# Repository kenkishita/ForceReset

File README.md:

#Arduino Force Reset  
This board has been connected between SWP1 of the RPi_SoftSwitch and Reset Pin of the Arduino (need soldering).  
The Foldarap-chimera is full controlled by OctoPrint, ATX power distribute control included. So, the Marlin firmware set up power off the initial,  and send M80 by Octoprint when connected.  
And, I added small program which send the M81 (Turn off Power Supply) after stopping of the Octoprint. But, sometime, it didn't work because connection failure of the /dev/ttyACM0.  
  
This board send reset signal to the arduino simultaneously without any side effect.   

##License Information

These files are free; you can redistribute them and/or modify them under the
terms of the Creative Commons Attribution-ShareAlike 4.0 International
License only, as published by the Creative Commons organization.  

These files are distributed in the hope that they will be useful, but
WITHOUT ANY WARRANTY; without even the implied warranty of MERCHANTABILITY
or FITNESS FOR A PARTICULAR PURPOSE.  See the Creative Commons Attribution-
ShareAlike 4.0 International License for more details.  

Please contact Aynik technology Co., Ltd. at kkishita@aynik-tech.jp if you need additional information or have any questions.

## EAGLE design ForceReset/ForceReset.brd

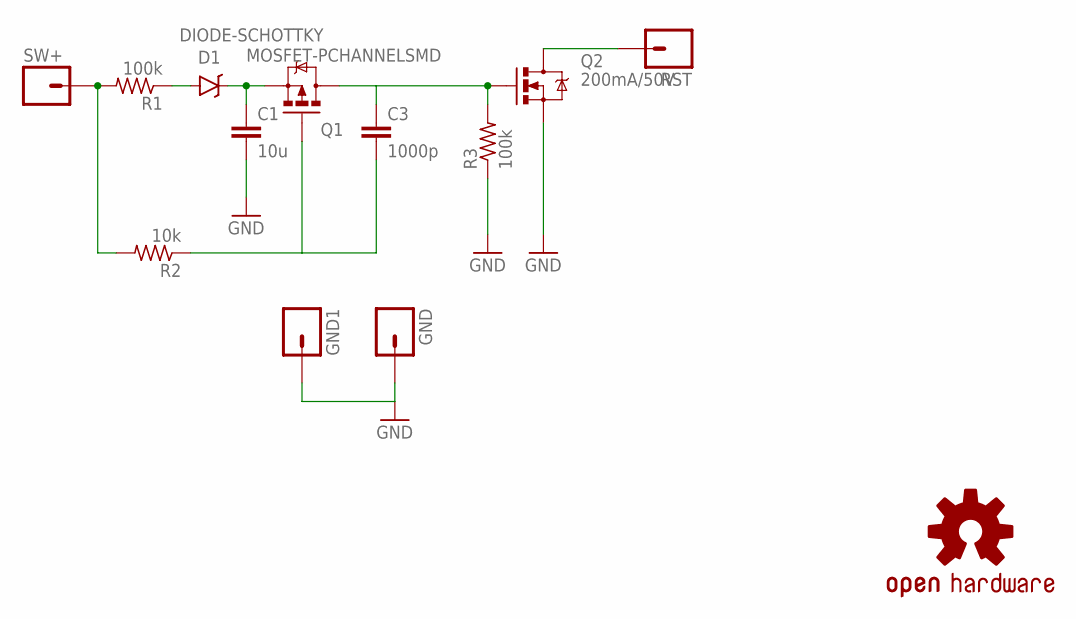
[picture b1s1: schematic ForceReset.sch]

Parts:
C1: 10u; 1608
C3: 1000p; 1608
D1: DIODE-SCHOTTKY; TUMD2
GND, GND1: M01PTH; 1X01
LOGO1: OSHW-LOGOS; OSHW-LOGO-S
Q1: MOSFET-PCHANNELSMD; SOT23-3
Q2: 200mA/50V; SOT23-3
R1, R3: 100k; 1608
R2: 10k; 1608
RST: M01PTH; 1X01
SW+: M01PTH; 1X01

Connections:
GND: C1.P$2 (2), GND.1, GND1.1, Q2.2 (S), R3.P$1 (1)
unnamed: R1.P$2 (2), R2.P$2 (2), SW+.1
unnamed: C1.P$1 (1), D1.C, Q1.2 (S)
unnamed: C3.P$1 (1), Q1.3 (D), Q2.1 (G), R3.P$2 (2)
unnamed: Q2.3 (D), RST.1
unnamed: C3.P$2 (2), Q1.1 (G), R2.P$1 (1)
unnamed: D1.A, R1.P$1 (1)

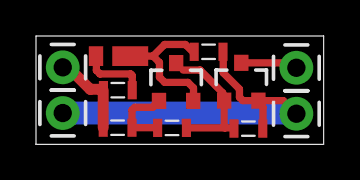
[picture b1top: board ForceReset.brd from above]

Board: 2 copper layers, 16.0 x 6.0 mm, 13 parts (1 on the bottom side), 7 nets.

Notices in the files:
parts and their libraries:
SparkFun-Connectors: Licensing: Creative Commons ShareAlike 4.0 International - https://creativecommons.org/licenses/by-sa/4.0
SparkFun: Licensing: CC v3.0 Share-Alike You are welcome to use this library for commercial purposes.
